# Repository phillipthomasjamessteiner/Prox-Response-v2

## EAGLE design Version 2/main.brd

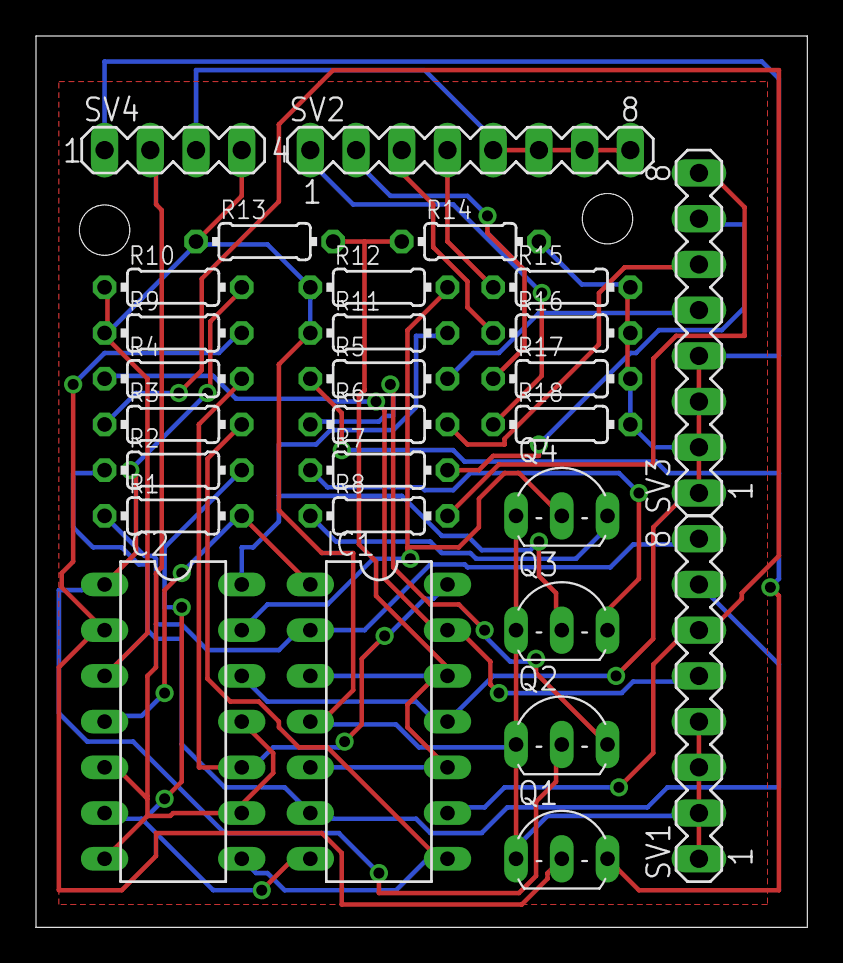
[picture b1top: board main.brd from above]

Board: 2 copper layers, 42.9 x 49.5 mm, 28 parts (0 on the bottom side), 29 nets.

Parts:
IC1: LM324N; DIL14
IC2: LM339N; DIL14
Q1, Q2, Q3, Q4: BC487; TO92-EBC
R1, R2, R3, R4: 68kΩ; 0204/7
R5, R6, R7, R8: 100Ω; 0204/7
R9, R10, R11, R12, R13, R14: 3k3Ω; 0204/7
R15, R16, R17, R18: 44Ω; 0204/7
SV1: Photodiode Connectors; MA08-1
SV2: IR LED Connectors; MA08-1
SV3: Visual LED Connector; MA08-1
SV4: Power In; MA04-1

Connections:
5V: IC1.4, IC2.3, Q1.C, Q2.C, Q3.C, Q4.C, R9.1, R10.1, R11.1, R12.1, R13.1, SV1.1, SV1.2, SV1.3, SV1.4, SV4.4
+1.84V: SV2.5, SV2.6, SV2.7, SV2.8, SV4.3
AS1: IC1.1, IC2.4, R1.2
AS2: IC1.7, IC2.6, R2.2
AS3: IC1.8, IC2.8, R3.2
AS4: IC1.14, IC2.10, R4.2
GND: IC1.11, IC2.12, R14.2, R15.2, R16.2, R17.2, R18.2, SV3.1, SV3.2, SV3.3, SV3.4, SV4.1
unnamed: Q1.E, R5.1
unnamed: Q2.E, R6.1
unnamed: Q3.E, R7.1
unnamed: Q4.E, R8.1
unnamed: R15.1, SV2.4
unnamed: R16.1, SV2.3
unnamed: R17.1, SV2.2
unnamed: R18.1, SV2.1
PD1: IC1.2, R1.1, SV1.8
PD2: IC1.6, R2.1, SV1.7
PD3: IC1.9, R3.1, SV1.6
PD4: IC1.13, R4.1, SV1.5
T1: IC2.2, Q1.B, R9.2
T2: IC2.1, Q2.B, R10.2
T3: IC2.14, Q3.B, R11.2
T4: IC2.13, Q4.B, R12.2
VGND: IC1.3, IC1.5, IC1.10, IC1.12, R13.2, R14.1
VLED1: R5.2, SV3.5
VLED2: R6.2, SV3.6
VLED3: R7.2, SV3.7
VLED4: R8.2, SV3.8
VLOGIC: IC2.5, IC2.7, IC2.9, IC2.11, SV4.2

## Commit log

2017-02-03 Added files 2-3-17
2017-02-04 Finished 2nd Version
2017-02-07 Final Version
2017-02-13 Power Supply Work
2017-02-13 Main 3d Attempt
2017-03-05 Update 3-4-17
2017-03-29 3-23-17 Periodic Push
